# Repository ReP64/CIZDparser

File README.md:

send data from a CI200Sc to a zebra printer ZD420 
the data from the CI200SC format is BP-DT4 Form0 
the programming for de ZD420 is ZPL format

    CI200SC settings
    F27 0           8N1
    F28 4           9600
    F29 1   F33 0   0=prt 1=pc
    F30 0   F34 0   22byte
    F31 1   F35 1   1 stream
    F40 3           BP-DT4 format
    F41 0         ` FORM0
    F42 0           manual print
    F43 1           line feed

    BP-DT4 format
    V00   NETWEIGHT   7
    V01   UNIT        2
    V02   GROSS       7
    V03   TARE        7
    V04   DATE        10
    V05   TIME        8
    V06   ID          2
    V07   COUNT       3
    V08   NET:BARCODE 6
    V09   TOTAL NET   9

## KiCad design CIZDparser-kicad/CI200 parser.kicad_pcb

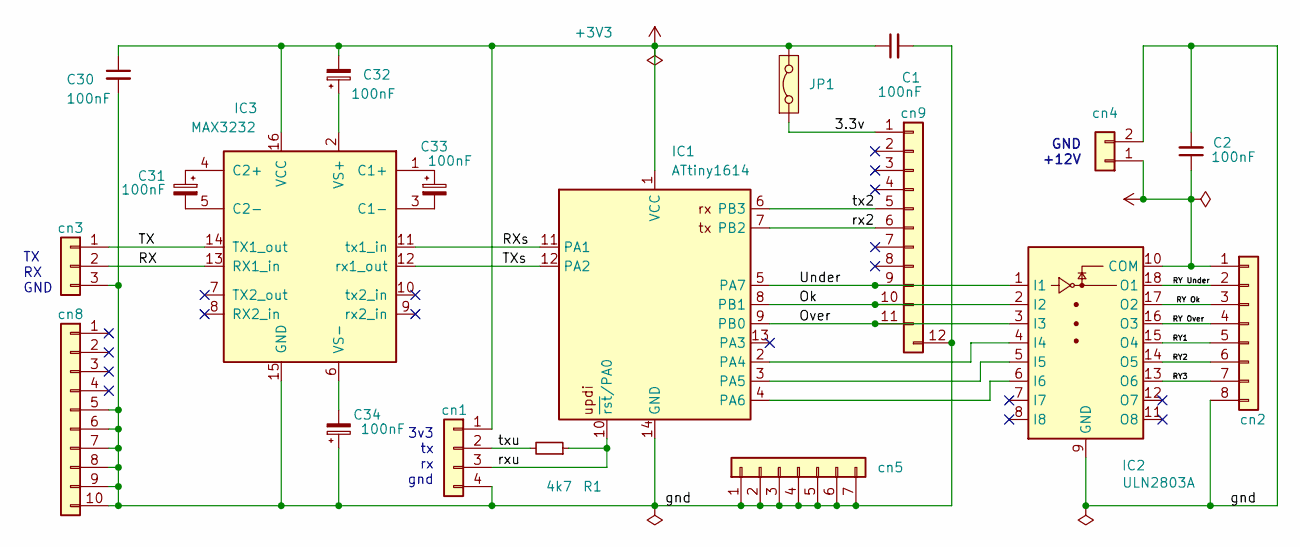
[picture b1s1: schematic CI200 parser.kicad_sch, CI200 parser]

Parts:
C1, C2, C30, C31, C32, C33, C34: 100nF; C_1206_3216Metric_Pad1.33x1.80mm_HandSolder
IC1: ATtiny1614; SOIC-14_3.9x8.7mm_P1.27mm
IC2: ULN2803A; SOP-18_7x12.5mm_P1.27mm
IC3: MAX3232; SOIC-16_3.9x9.9mm_P1.27mm
JP1: Jumper_2_Bridged; PinHeader_2x01_P2.54mm_Vertical
R1: 4k7; R_1206_3216Metric_Pad1.30x1.75mm_HandSolder
cn1: Conn_01x04; PinSocket_1x04_P2.54mm_Vertical
cn2, cn5: Conn_01x07; PinSocket_1x07_P2.54mm_Vertical
cn3: Conn_01x03; PinSocket_1x03_P2.54mm_Vertical
cn4: Conn_01x02; PinSocket_1x02_P2.54mm_Vertical
cn8: Conn_01x10; PinSocket_1x10_P2.54mm_Vertical
cn9: Conn_01x12; PinSocket_1x12_P2.54mm_Vertical

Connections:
+3V3: C1.1, C30.1, C32.2, IC1.1 (VCC), IC3.16 (VCC), JP1.2 (B), cn1.1; also elsewhere on the board
+12V: C2.1, IC2.10 (COM), cn2.1, cn4.1
/3.3v: JP1.1 (A), cn9.1; also elsewhere on the board
/Ok: IC1.8 (PB1), IC2.2 (I2), cn9.10
/Over: IC1.9 (PB0), IC2.3 (I3), cn9.11
/RX: IC3.13 (RX1_in), cn3.2
/RXs: IC1.11 (PA1), IC3.11 (tx1_in)
/RY1: IC2.15 (O4), cn2.5
/RY2: IC2.14 (O5), cn2.6
/RY3: IC2.13 (O6), cn2.7
/RY Ok: IC2.17 (O2), cn2.3
/RY Over: IC2.16 (O3), cn2.4
/RY Under: IC2.18 (O1), cn2.2
/TX: IC3.14 (TX1_out), cn3.1
/TXs: IC1.12 (PA2), IC3.12 (rx1_out)
/Under: IC1.5 (PA7), IC2.1 (I1), cn9.9
/gnd: C1.2, C2.2, C30.2, C34.1, IC1.14 (GND), IC2.9 (GND), IC3.15 (GND), cn1.4, cn2.8, cn3.3, cn4.2, cn5.1, cn5.2, cn5.3, cn5.4, cn5.5, cn5.6, cn5.7, cn8.5, cn8.6, cn8.7, cn8.8, cn8.9, cn8.10, cn9.12
/rx2: IC1.7 (PB2), cn9.6
/rxu: IC1.10 (~rst/PA0), R1.1, cn1.3
/tx2: IC1.6 (PB3), cn9.5
/txu: R1.2, cn1.2
unnamed: IC1.2 (PA4), IC2.4 (I4)
unnamed: IC1.3 (PA5), IC2.5 (I5)
unnamed: IC1.4 (PA6), IC2.6 (I6)
unnamed: C33.1, IC3.1 (C1+)
unnamed: C33.2, IC3.3 (C1-)
unnamed: C31.1, IC3.4 (C2+)
unnamed: C31.2, IC3.5 (C2-)
unnamed: C32.1, IC3.2 (VS+)
unnamed: C34.2, IC3.6 (VS-)

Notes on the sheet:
3v3 tx rx gnd
TX RX GND
GND +12V

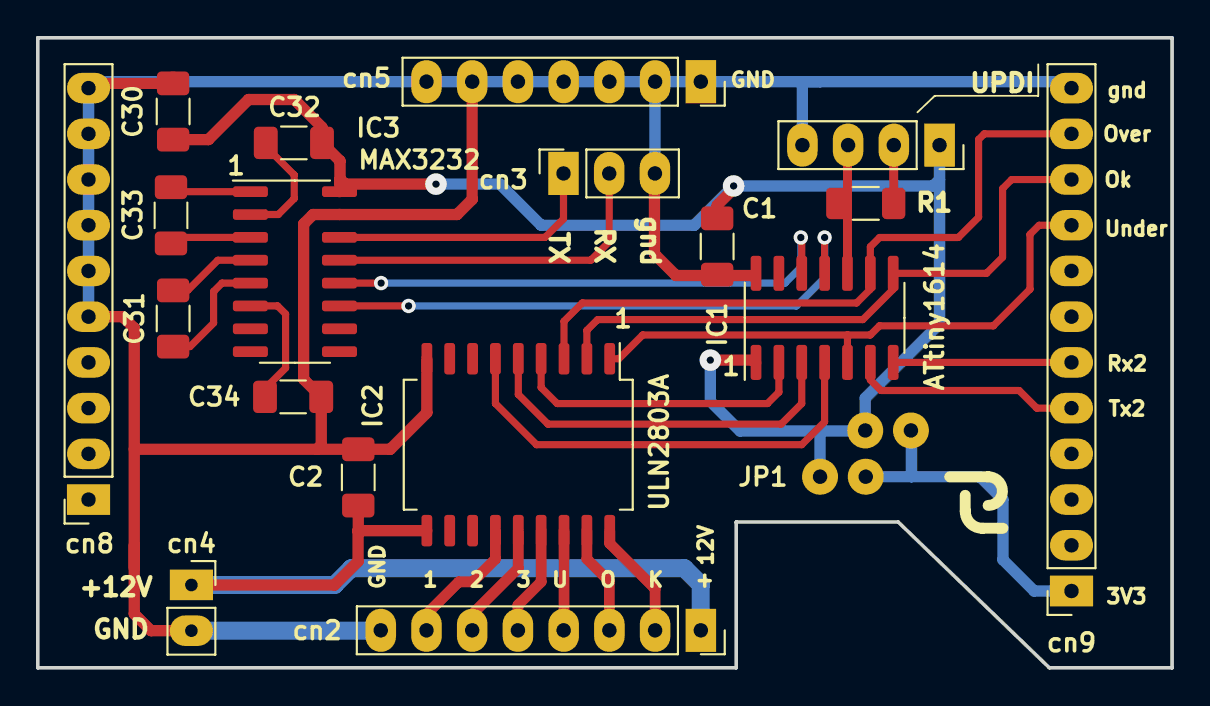
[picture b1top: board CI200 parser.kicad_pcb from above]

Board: 2 copper layers, 63.0 x 35.0 mm, 22 parts (1 on the bottom side), 30 nets.

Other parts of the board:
JP1#2: Jumper_2_Bridged; PinHeader_2x01_P2.54mm_Vertical
REF1, REF1#2: ReP_Silk

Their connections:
+3V3: JP1#2.2 (B); also elsewhere on the board
/3.3v: JP1#2.1 (A); also elsewhere on the board

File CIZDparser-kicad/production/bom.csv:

Designator,Footprint,Quantity,Value,LCSC Part #
"C1, C2, C30, C31, C32, C33, C34",1206,7,100nF,
CN1,PinSocket_1x04_P2.54mm_Vertical,1,Conn_01x04,
CN2,PinSocket_1x08_P2.54mm_Vertical,1,Conn_01x07,
CN3,PinSocket_1x03_P2.54mm_Vertical,1,Conn_01x03,
CN4,PinSocket_1x02_P2.54mm_Vertical,1,Conn_01x02,
CN5,PinSocket_1x07_P2.54mm_Vertical,1,Conn_01x07,
CN8,PinSocket_1x10_P2.54mm_Vertical,1,Conn_01x10,
CN9,PinSocket_1x12_P2.54mm_Vertical,1,Conn_01x12,
IC1,SOIC-14_3.9x8.7mm_P1.27mm,1,ATtiny1614,
IC2,SOP-18_7x12.5mm_P1.27mm,1,ULN2803A,
IC3,SOIC-16_3.9x9.9mm_P1.27mm,1,MAX3232,
"JP1_2, JP1",PinHeader_2x01_P2.54mm_Vertical,2,Jumper_2_Bridged,
R1,1206,1,4k7,
"REF1_2, REF1",ReP_Silk,2,ReP_Silk,
